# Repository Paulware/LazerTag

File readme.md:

<H3>Hardware</H3>
<ul>
<li> Arduino Shield with IR Transmit and receive</li>
<ul>
<li>Fritzing Diagrama</li>
<li>Eagle schematic and board</li>
<li>Gerber .zip file (Iteadstudio.com) can create pcb</li>
</ul>
</ul>
<H3>Software</H3>
<ul>
<li>LazerTag.ino sketch to send and receive pulses</li>
<li>libraries</li>
<ul>
<li>IR - Basic IR Sampling library</li>
<li>IRLazer - Lazer tab receive and transmit</li>
</ul>
</ul>
<hr>
Future:
  Add :
    IR "grenades"
    Capture the ir "flag"

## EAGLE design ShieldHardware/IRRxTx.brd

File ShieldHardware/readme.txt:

11/3/2014
    Red LED should be marked because infra-red emitters also look like leds.
    IR Tx leds should be rotated 90 degrees so they can be bent without shorting
    3V regulator LD33V has incorrect part in schematic.  Its a sparkfun part.
    Pinout was incorrectly for LM7805 regulator 
    Ready for reorder (not urgent)
    To assemble, shift LD part one pin, unused pin goes to first pin(VCC)
    
11/6/2014
    16 mhz clock and 10k resistor moved to top of pcb so that the unit 
    can be glued to a flat surface.  Added standoff holes .
    
11/7/2014
    Added 8 and 6 pin headers in case this could be used like a DIY Arduino.  Moved
    standoffs more to the corner.

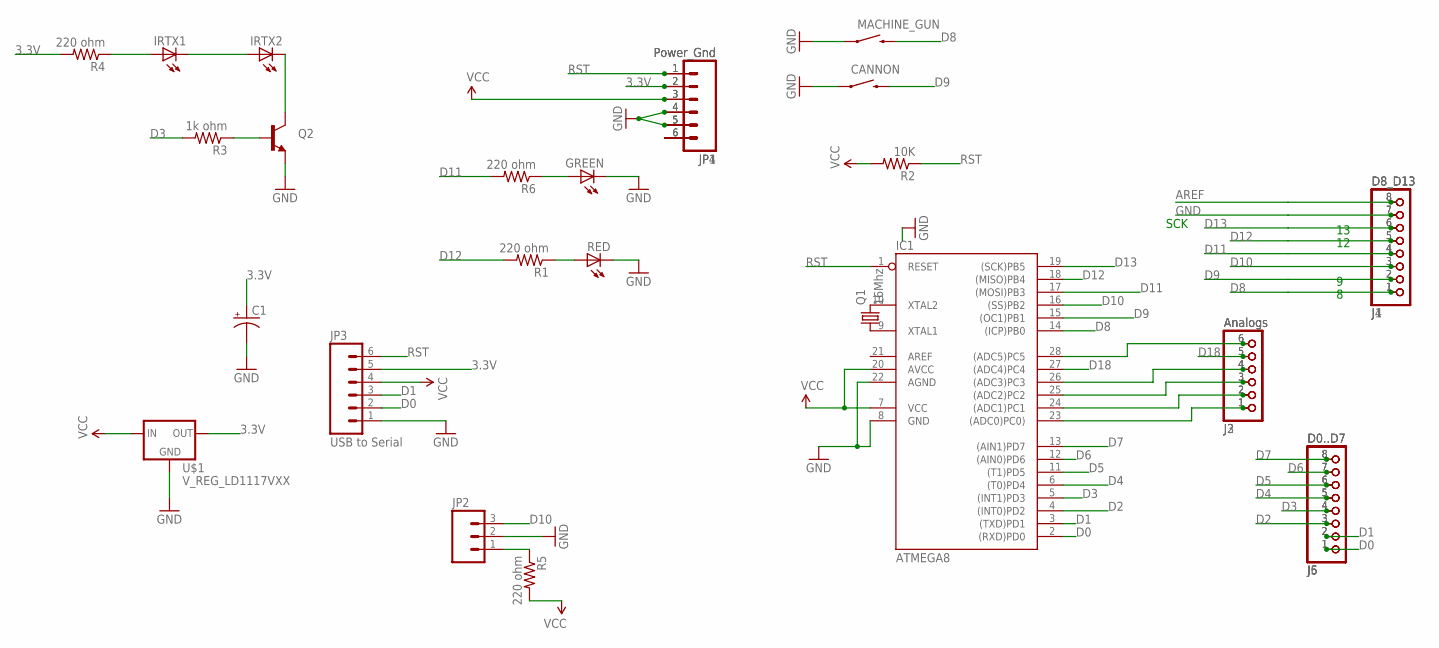
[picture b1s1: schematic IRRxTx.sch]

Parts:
C1: CAP_POLPTH2; CPOL-RADIAL-10UF-25V
CANNON: SWITCH-MOMENTARY-2PTH; TACTILE-PTH
GREEN: LED5MM
IC1: ATMEGA8; DIL28-3
IRTX1, IRTX2: LED5MM
J1, J4: D8_D13; 1X08
J2, J3: Analogs; 1X06
J5, J6: D0..D7; 1X08
JP1, JP4: Power_Gnd; 1X06
JP2: M03PTH; 1X03
JP3: USB to Serial; 1X06
MACHINE_GUN: SWITCH-MOMENTARY-2PTH; TACTILE-PTH
Q1: 16Mhz; HC49US
Q2: TRANSISTOR_NPNTO92; TO-92
R1, R4, R5, R6: 220 ohm; AXIAL-0.3
R2: 10K; AXIAL-0.3
R3: 1k ohm; AXIAL-0.3
RED: LED5MM
U$1: V_REG_LD1117VXX; 78XXL

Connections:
3.3V: C1.1 (+), JP1.2, JP3.5, JP4.2, R4.P$2 (2), U$1.GND (OUT)
AREF: IC1.21 (AREF), J1.8, J4.8
D0: IC1.2 ((RXD)PD0), J5.1, J6.1, JP3.2
D1: IC1.3 ((TXD)PD1), J5.2, J6.2, JP3.3
D2: IC1.4 ((INT0)PD2), J5.3, J6.3
D3: IC1.5 ((INT1)PD3), J5.4, J6.4, R3.P$2 (2)
D4: IC1.6 ((T0)PD4), J5.5, J6.5
D5: IC1.11 ((T1)PD5), J5.6, J6.6
D6: IC1.12 ((AIN0)PD6), J5.7, J6.7
D7: IC1.13 ((AIN1)PD7), J5.8, J6.8
D8: IC1.14 ((ICP)PB0), J1.1, J4.1, MACHINE_GUN.3 (2)
D9: CANNON.3 (2), IC1.15 ((OC1)PB1), J1.2, J4.2
D10: IC1.16 ((SS)PB2), J1.3, J4.3, JP2.3
D11: IC1.17 ((MOSI)PB3), J1.4, J4.4, R6.P$2 (2)
D12: IC1.18 ((MISO)PB4), J1.5, J4.5, R1.P$2 (2)
D13: IC1.19 ((SCK)PB5), J1.6, J4.6
D18: IC1.27 ((ADC4)PC4), J2.5, J3.5
GND: C1.2 (-), CANNON.1, GREEN.K (C), IC1.8 (GND), IC1.22 (AGND), J1.7, J4.7, JP1.4, JP1.5, JP2.2, JP3.1, JP4.4, JP4.5, MACHINE_GUN.1, Q2.1 (E), RED.K (C), U$1.IN (GND)
unnamed: IC1.10 (XTAL2), Q1.2
unnamed: IC1.9 (XTAL1), Q1.1
unnamed: R1.P$1 (1), RED.A
unnamed: Q2.2 (B), R3.P$1 (1)
unnamed: IRTX2.K (C), Q2.3 (C)
unnamed: IRTX1.K (C), IRTX2.A
unnamed: IRTX1.A, R4.P$1 (1)
unnamed: JP2.1, R5.P$1 (1)
unnamed: GREEN.A, R6.P$1 (1)
unnamed: JP1.6, JP4.6
unnamed: IC1.23 ((ADC0)PC0)), J2.1, J3.1
unnamed: IC1.24 ((ADC1)PC1), J2.2, J3.2
unnamed: IC1.25 ((ADC2)PC2), J2.3, J3.3
unnamed: IC1.26 ((ADC3)PC3), J2.4, J3.4
unnamed: IC1.28 ((ADC5)PC5), J2.6, J3.6
RST: IC1.1 (RESET), JP1.1, JP3.6, JP4.1, R2.P$1 (1)
VCC: IC1.7 (VCC), IC1.20 (AVCC), JP1.3, JP3.4, JP4.3, R2.P$2 (2), R5.P$2 (2), U$1.OUT (IN)

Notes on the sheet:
SCK

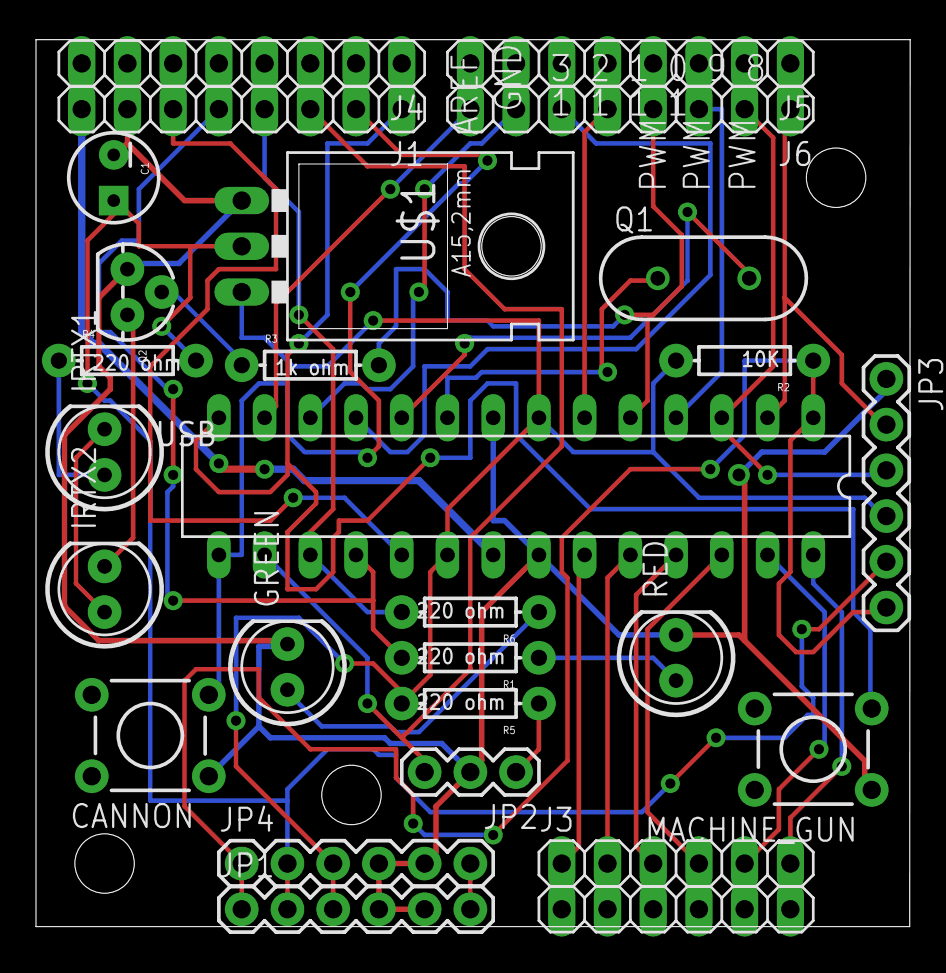
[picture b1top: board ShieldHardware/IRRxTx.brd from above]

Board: 2 copper layers, 48.6 x 49.3 mm, 30 parts (0 on the bottom side), 35 nets.

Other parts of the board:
U$2, U$3, U$4: STAND-OFF

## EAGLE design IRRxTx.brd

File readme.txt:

Created 10/19. 
   Started Software

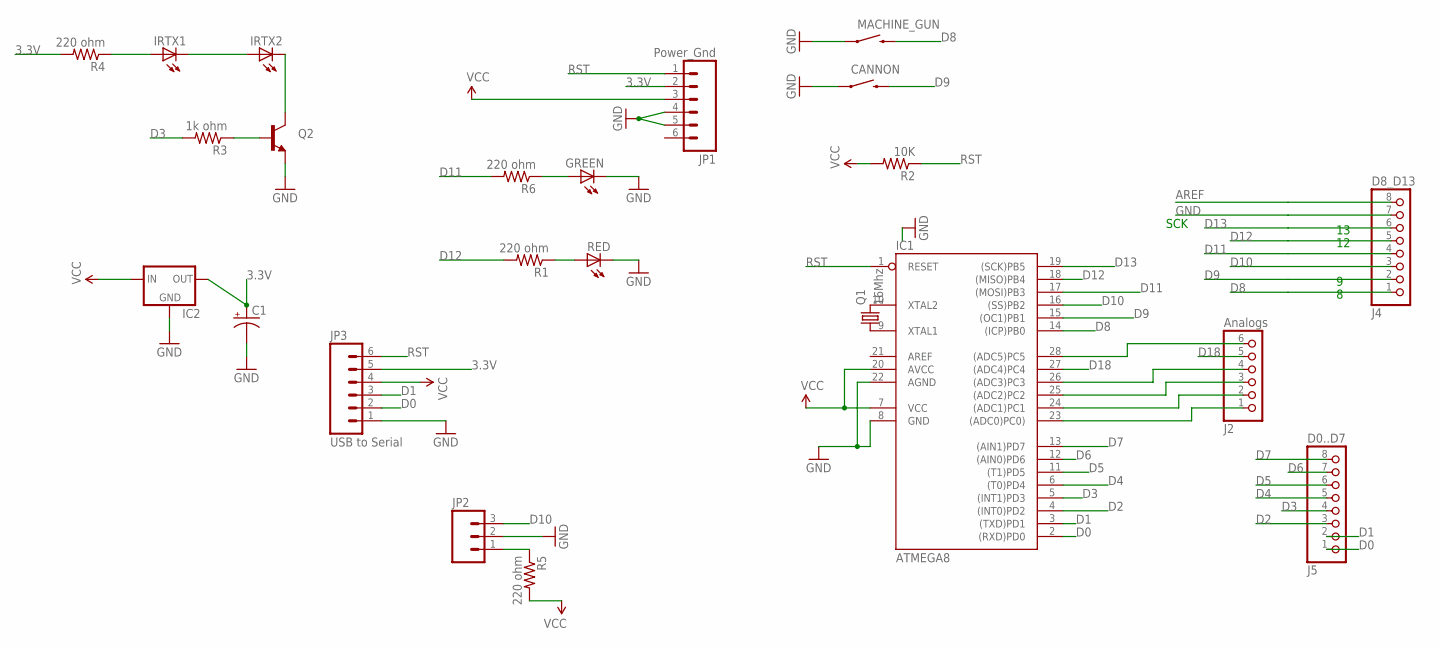
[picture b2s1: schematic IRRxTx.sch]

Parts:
C1: CAP_POLPTH2; CPOL-RADIAL-10UF-25V
CANNON: SWITCH-MOMENTARY-2PTH; TACTILE-PTH
GREEN: LED5MM
IC1: ATMEGA8; DIL28-3
IC2: V_REG_78XXSIDE; 78XXL
IRTX1, IRTX2: LED5MM
J2: Analogs; 1X06
J4: D8_D13; 1X08
J5: D0..D7; 1X08
JP1: Power_Gnd; 1X06
JP2: M03PTH; 1X03
JP3: USB to Serial; 1X06
MACHINE_GUN: SWITCH-MOMENTARY-2PTH; TACTILE-PTH
Q1: 16Mhz; HC49US
Q2: TRANSISTOR_NPNTO92; TO-92
R1, R4, R5, R6: 220 ohm; AXIAL-0.3
R2: 10K; AXIAL-0.3
R3: 1k ohm; AXIAL-0.3
RED: LED5MM

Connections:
3.3V: C1.1 (+), IC2.OUT, JP1.2, JP3.5, R4.P$2 (2)
AREF: IC1.21 (AREF), J4.8
D0: IC1.2 ((RXD)PD0), J5.1, JP3.2
D1: IC1.3 ((TXD)PD1), J5.2, JP3.3
D2: IC1.4 ((INT0)PD2), J5.3
D3: IC1.5 ((INT1)PD3), J5.4, R3.P$2 (2)
D4: IC1.6 ((T0)PD4), J5.5
D5: IC1.11 ((T1)PD5), J5.6
D6: IC1.12 ((AIN0)PD6), J5.7
D7: IC1.13 ((AIN1)PD7), J5.8
D8: IC1.14 ((ICP)PB0), J4.1, MACHINE_GUN.3 (2)
D9: CANNON.3 (2), IC1.15 ((OC1)PB1), J4.2
D10: IC1.16 ((SS)PB2), J4.3, JP2.3
D11: IC1.17 ((MOSI)PB3), J4.4, R6.P$2 (2)
D12: IC1.18 ((MISO)PB4), J4.5, R1.P$2 (2)
D13: IC1.19 ((SCK)PB5), J4.6
D18: IC1.27 ((ADC4)PC4), J2.5
GND: C1.2 (-), CANNON.1, GREEN.K (C), IC1.8 (GND), IC1.22 (AGND), IC2.GND, J4.7, JP1.4, JP1.5, JP2.2, JP3.1, MACHINE_GUN.1, Q2.1 (E), RED.K (C)
unnamed: IC1.10 (XTAL2), Q1.2
unnamed: IC1.9 (XTAL1), Q1.1
unnamed: R1.P$1 (1), RED.A
unnamed: Q2.2 (B), R3.P$1 (1)
unnamed: IRTX2.K (C), Q2.3 (C)
unnamed: IRTX1.K (C), IRTX2.A
unnamed: IRTX1.A, R4.P$1 (1)
unnamed: JP2.1, R5.P$1 (1)
unnamed: GREEN.A, R6.P$1 (1)
unnamed: IC1.23 ((ADC0)PC0)), J2.1
unnamed: IC1.24 ((ADC1)PC1), J2.2
unnamed: IC1.25 ((ADC2)PC2), J2.3
unnamed: IC1.26 ((ADC3)PC3), J2.4
unnamed: IC1.28 ((ADC5)PC5), J2.6
RST: IC1.1 (RESET), JP1.1, JP3.6, R2.P$1 (1)
VCC: IC1.7 (VCC), IC1.20 (AVCC), IC2.IN, JP1.3, JP3.4, R2.P$2 (2), R5.P$2 (2)

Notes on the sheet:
SCK

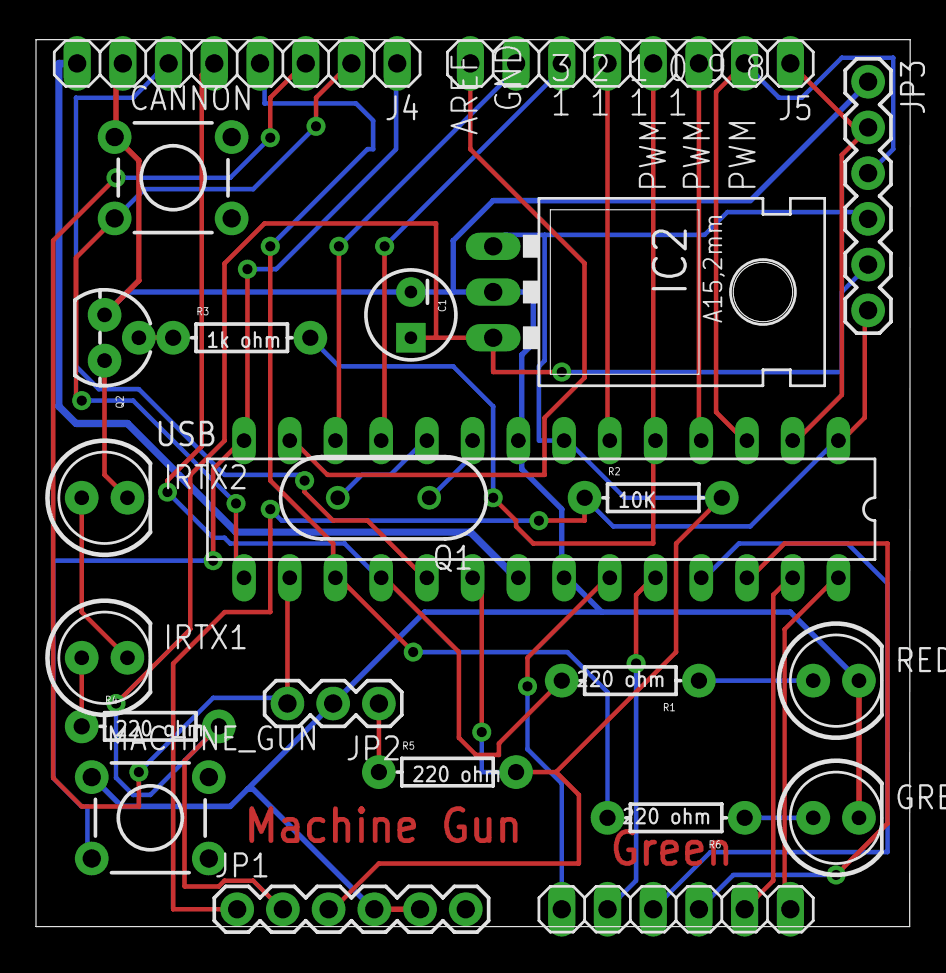
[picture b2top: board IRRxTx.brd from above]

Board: 2 copper layers, 48.6 x 49.3 mm, 23 parts (0 on the bottom side), 34 nets.

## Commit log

2014-10-19 :space_invader: Added .gitattributes & .gitignore files
2014-10-19 Initial Creation
    Add Fritzing file, eagle schematic, sketches and libraries
2014-10-19 v0.02
    Updaetd readme.md
2014-10-20 v0.03
    Added IRLazer library directory
    Can now shoot and heal (reset)
2014-10-20 v0.04
    Modified Readme file, organized file directories
2014-10-31 v0.05
    Added "Grenade" project
2014-11-05 v0.06
    Updated Schematic
2014-11-09 v.0.07
    Added Grenade
